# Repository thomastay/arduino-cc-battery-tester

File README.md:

# arduino-cc-battery-tester
Constant current circuit to test 18650 batteries.

## Introduction
18650 batteries need to be tested under load to know their capacity. It is possible to plot a discharge curve of the battery, but a constant current load gives you more useful data as you will be using the 18650 battery to draw a certain amount of current in your circuit anyway. 

The circuit diagram can be seen in "BJT CC.sch". Basically, the op-amp and the transistor (a TIP120 is used here, but any power Darlington would work too) act as a constant-current load, keeping the current at 1 amp through the 1ohm power resistor. 

The important part of the circuit is that it is controlled by an Arduino. The Arduino senses the battery voltage and switches off the transistor once it reaches a set cutoff point as an over-discharge protection. This is crucial since we are dealing with unprotected 18650 batteries. 

## Important variables

The most important variable is "const float currentSet", which sets the current in Amps. Set it to 1.0 to test your battery under 1A. 

## Usage
Set the variable currentSet and upload the code to your arduino. Then, connect the wires to your Arduino as shown in the schematic. You can monitor your Arduino from the serial monitor, or you can use a program like PLX-DAQ, which logs the serial monitor data to an Excel file.

When the battery is under load, the LED will turn on. After the battery is discharged, the battery cuts off and the LED will blink once a second, indicating that the discharge is done.

Here's how to calculate the capacity of the battery: Take the time in hours that the battery works under load, and multiply it by 1000 to get the capacity in mAh. This is the capacity of your battery under a 1A load.

## LED indicator

1 blink every 5 seconds --> No battery connected

2 blinks every second, for 3 seconds, followed by 2 second delay --> Battery undercharged

3 blinks every second, for 3 seconds, followed by 2 second delay --> Battery overcharged

1 blink every second --> Battery finished discharging

LED fully on --> Battery under load. 

## Credits:
I was heavily inspired by GreatScott's video, and my circuit is almost identical to his. Check out his video here: https://www.youtube.com/watch?v=8uBcywBUTkw

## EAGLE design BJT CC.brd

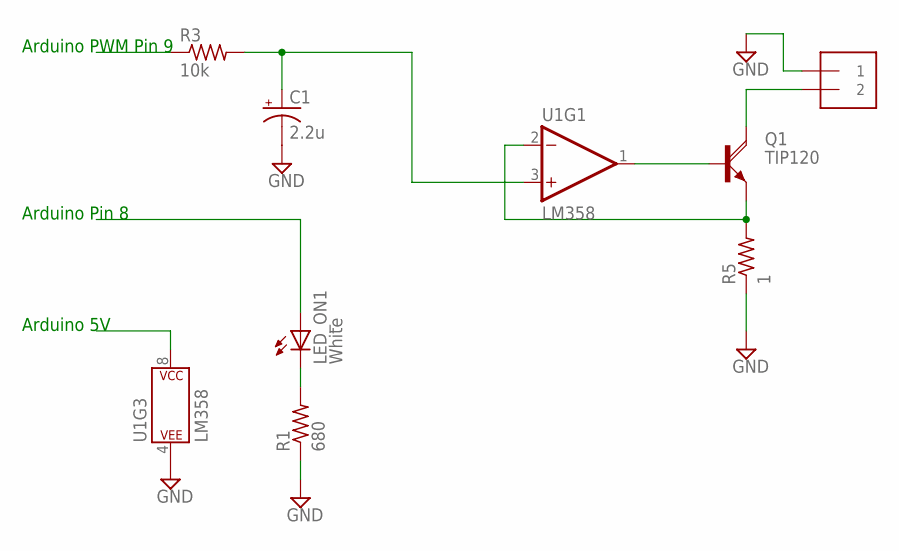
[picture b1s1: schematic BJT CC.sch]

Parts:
BAT_IN: 1X2-3.5MM
C1: 2.2u; E2-4
LED_ON1: White; LED5MM
Q1: TIP120; TO220AH
R1: 680; 0207/10
R3: 10k; 0207/10
R5: 1; 0922/22
U1: LM358; DIP08

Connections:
GND: BAT_IN.1, C1.-, R1.1, R5.1, U1.4 (P$V-)
unnamed: LED_ON1.K (C), R1.2
unnamed: C1.+, R3.2, U1.3 (+IN)
unnamed: Q1.B, U1.1 (OUT)
unnamed: BAT_IN.2, Q1.C
unnamed: Q1.E, R5.2, U1.2 (-IN)

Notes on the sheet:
Arduino Pin 8
Arduino PWM Pin 9
Arduino 5V

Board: 2 copper layers, 8 parts (0 on the bottom side), 6 nets, no tracks yet.

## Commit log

2017-08-07 Files
    These are the files needed for the constant current driver
2017-08-08 Updated instructions
    Updated instructions
2017-08-08 changes
    changes
2017-08-08 readmechanges
    changes
2017-08-08 Errors
    fixed errors
2017-08-08 Updated values
    Updated values

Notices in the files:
parts and their libraries:
SparkFun-IC-Amplifiers: Licensing: Creative Commons ShareAlike 4.0 International - https://creativecommons.org/licenses/by-sa/4.0
